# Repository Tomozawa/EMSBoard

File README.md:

# EMSBoard
[BaseBoard ver4.0](https://github.com/tk20e/Base-Board-ver4.0-hw.git)上のBluePillにEMS信号を入力できるようにする基板です。

STM32F103C6T6Aが載っているBluePillを想定しています。これ以外の基板を使用する場合、EMSが入力されるピンが5Vトレラントであることを確認してください。

EMS信号はPA4に入力され、論理は以下の通りです。
| 状態 | ピン電圧 |
| ---- | ---- |
| 平常 | HIGH |
| 異常 | LOW |

作り方は以下の通りです。
1. R、Dが付いた部品をはんだ付けする(部品番号はBaseBoard ver4.0)と合わせてあります。
1. [2P平型のXHポスト](https://akizukidenshi.com/catalog/g/gC-12262/)をつける
1. [ピンヘッダ](https://akizukidenshi.com/catalog/g/gC-07199/)をつける(リンク先は10Pだが20Pがあるとなおよい)(足が長いタイプを購入すること)

使い方は以下の通りです。
1. BaseBoardを挿入するピンソケットにEMSBoardを挿入する。この際、EMSBoard上のXHポストがBaseBoard上のXHポストの方を向くようにする。
1. [XHハーネス(自作してもいい)](https://www.sengoku.co.jp/mod/sgk_cart/detail.php?code=EEHD-5BA7)で、BaseBoardのEmergencyボタンを付けるポストと、EMSBoardのポストを接続する(クロス配線でもストレート配線でもOK)(かならずU2に近い方のコネクタに挿す。逆にするとボタンに対して反応しない)
1. 残ったポストにはボタンを接続するか、何もつけないでおく
1. ボタンを操作するとEMSBoard上の赤色LEDが点灯したり消えたりすることを確認する

## 注意点
- BaseBoardが複数あり、すでに他のBaseBoard上に非常停止ボタンがつながっている場合、EMSBoardと接続されていない側のポストには非常停止ボタンがつけられません。
- 初期版(ver1.0)では誤ってPB10をEMS入力としていたため、初期版とそれ以降ではEMS入力ピンが異なります。
- 初期版(ver1.0)では、BaseBoard上のDIN_Fに当たるピン(PB10)をEMS入力として使用しているために、当該ピンは入出力として使えません。初期版は非推奨です。

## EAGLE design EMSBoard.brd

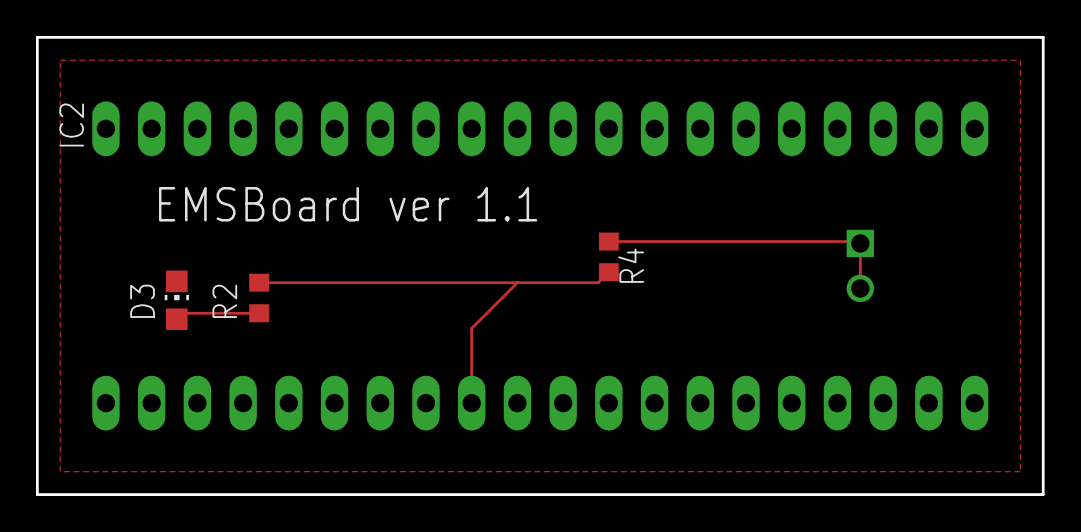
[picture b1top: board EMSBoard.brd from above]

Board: 2 copper layers, 55.9 x 25.4 mm, 5 parts (1 on the bottom side), 4 nets.

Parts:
D3: CHIP-LED0805
IC2: BLUE_PILL
J1: S2B-XH-A
R2: 1k; R0603
R4: 100; R0603

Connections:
GND: D3.C, IC2.P$19, IC2.P$20, IC2.P$39
unnamed: D3.A, R2.1
unnamed: J1.1, J1.2, R4.1
unnamed: IC2.P$9, R2.2, R4.2

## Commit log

2022-12-14 Resolve Conflicts
2022-12-14 Solid Ground
2022-12-14 Update Gabar Data
2023-02-18 EMS Pin is changed
2023-02-18 Minor change
